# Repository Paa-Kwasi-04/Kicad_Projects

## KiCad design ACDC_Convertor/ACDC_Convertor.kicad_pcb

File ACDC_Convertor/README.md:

# ACDC Convertor

## Description
This is an AC-to-DC converter (rectifier) circuit board designed to convert alternating current (AC) to direct current (DC). The board includes rectification, filtering, and voltage regulation components to provide a stable DC output from an AC input source.

## Features
- AC to DC power conversion
- Filtering and voltage regulation
- Suitable for powering DC electronic devices from AC mains
- Compact PCB design

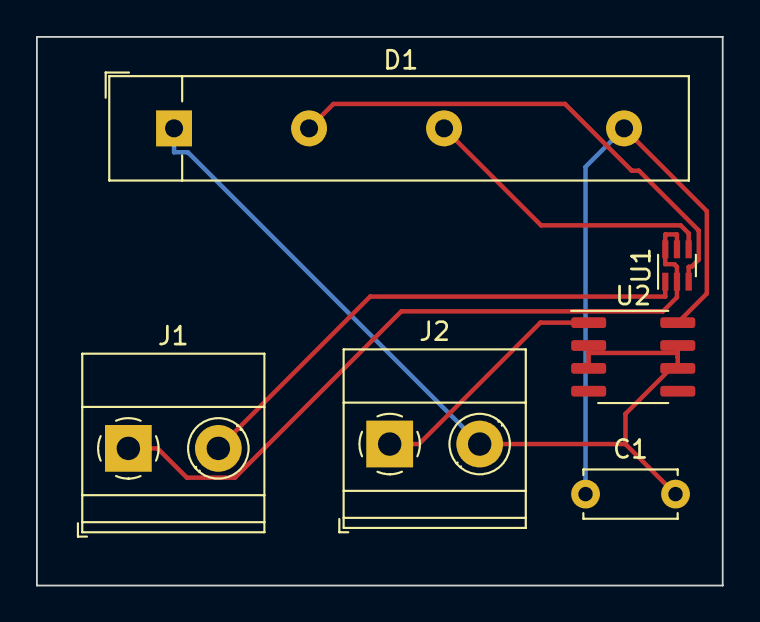
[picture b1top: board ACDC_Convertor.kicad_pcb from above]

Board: 2 copper layers, 38.1 x 30.5 mm, 6 parts (0 on the bottom side), 7 nets.

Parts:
C1: 100n; C_Disc_D5.0mm_W2.5mm_P5.00mm
D1: B40C5000-3x00A; Diode_Bridge_32.0x5.6x17.0mm_P10.0mm_P7.5mm
J1, J2: Screw_Terminal_01x02; TerminalBlock_Phoenix_MKDS-1,5-2_1x02_P5.00mm_Horizontal
U1: 0433BM15A0001; Balun_Johanson_0896BM15A0001
U2: L78L12_SO8; SOIC-8_3.9x4.9mm_P1.27mm

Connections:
unnamed: C1.1, D1.4 (+), U2.8 (IN)
unnamed: C1.2, D1.1 (-), J2.2, U2.2 (GND), U2.3 (GND), U2.6 (GND), U2.7 (GND)
unnamed: D1.2, U1.3
unnamed: D1.3, U1.4
unnamed: J1.1, U1.2 (GND), U1.5 (GND), U1.6 (GND)
unnamed: J1.2, U1.1
unnamed: J2.1, U2.1 (OUT)

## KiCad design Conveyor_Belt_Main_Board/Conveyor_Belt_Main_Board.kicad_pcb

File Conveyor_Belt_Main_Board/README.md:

# Conveyor Belt Main Board

## Description
This is the main control board for an automated conveyor belt system. The board features an ATmega328P microcontroller, TB6600 stepper motor driver interface, I2C multiplexer (TCA9548A) for managing multiple sensors, and various connectors for IR sensors and control inputs. It provides complete control and monitoring for industrial or automated conveyor systems.

## Features
- ATmega328P microcontroller for main control
- TB6600 stepper motor driver integration
- TCA9548A I2C multiplexer for multiple sensor channels (8 channels)
- E3F1-3DN1 IR sensor support for object detection
- 5V/5A buck converter for power regulation
- ISP programming header
- Multiple sensor and control connectors
- Reset and start/stop button inputs

## Components
See the [List of Components](List%20Of%20Components.txt) for detailed component specifications.

## Block Diagram

## PCB Design

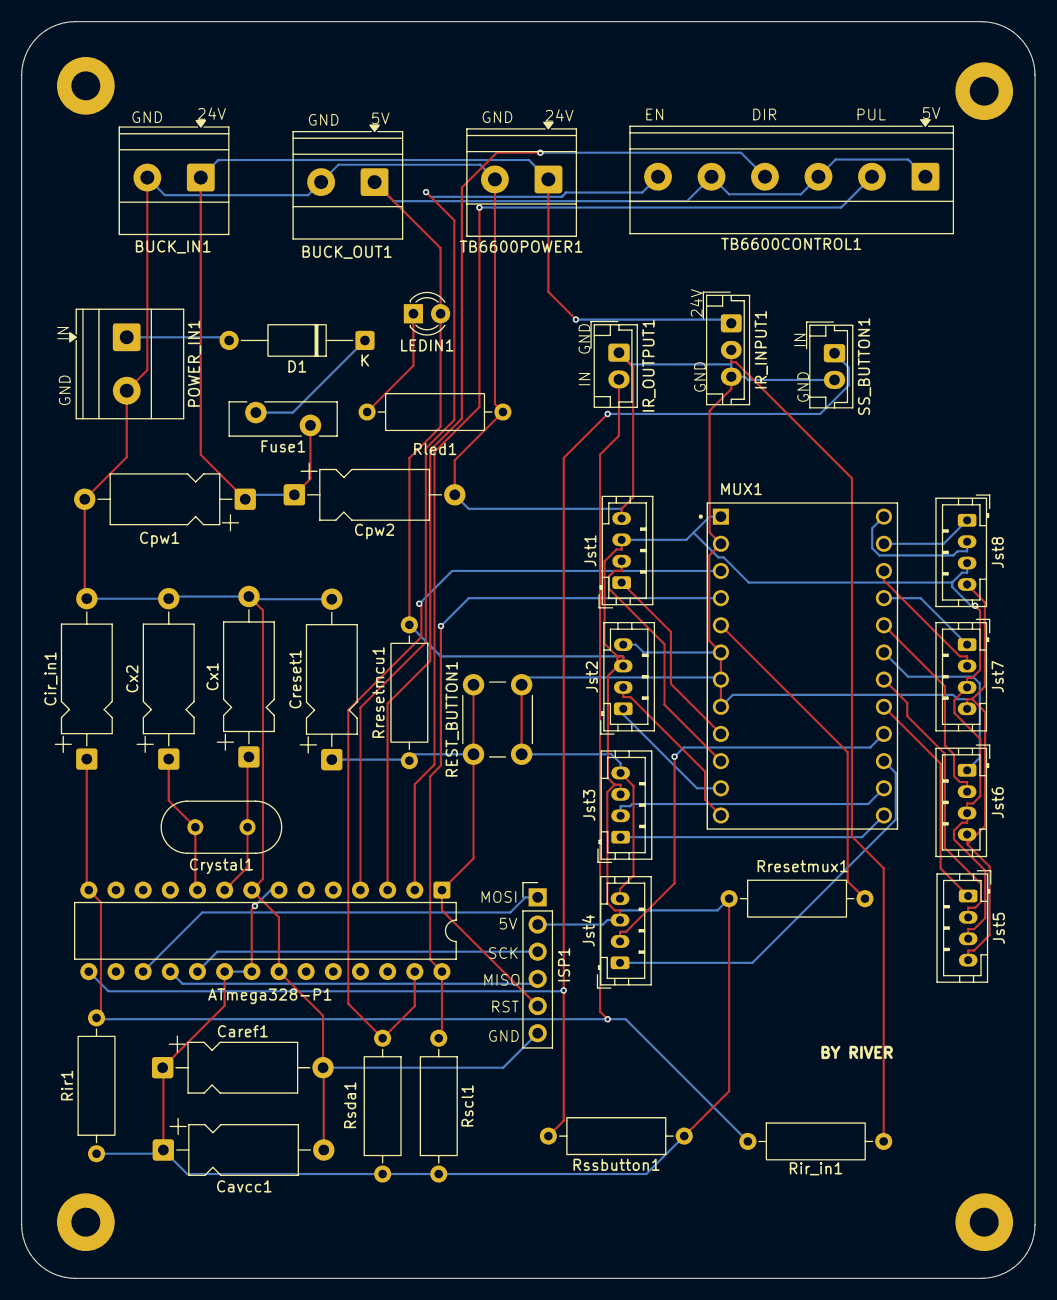
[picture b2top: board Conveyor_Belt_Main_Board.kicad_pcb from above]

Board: 2 copper layers, 94.8 x 117.5 mm, 44 parts (0 on the bottom side), 37 nets.

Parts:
ATmega328-P1: ATmega328-P; DIP-28_W7.62mm
BUCK_IN1: IN24V; TerminalBlock_Phoenix_MKDS-1,5-2_1x02_P5.00mm_Horizontal
BUCK_OUT1: OUT5V; TerminalBlock_Phoenix_MKDS-1,5-2_1x02_P5.00mm_Horizontal
Caref1: 10nF; CP_Axial_L10.0mm_D4.5mm_P15.00mm_Horizontal
Cavcc1: 0.1uF; CP_Axial_L10.0mm_D4.5mm_P15.00mm_Horizontal
Cir_in1: 10uF; CP_Axial_L10.0mm_D4.5mm_P15.00mm_Horizontal
Cpw1: 470uF; CP_Axial_L10.0mm_D4.5mm_P15.00mm_Horizontal
Cpw2: 0.1uF; CP_Axial_L10.0mm_D4.5mm_P15.00mm_Horizontal
Creset1: 0.1uF; CP_Axial_L10.0mm_D4.5mm_P15.00mm_Horizontal
Crystal1: 16MHz; Crystal_HC49-4H_Vertical
Cx1, Cx2: 22pF; CP_Axial_L10.0mm_D4.5mm_P15.00mm_Horizontal
D1: D1sch; D_A-405_P12.70mm_Horizontal
Fuse1: PTCFuse; Fuse_Bourns_MF-RG400
H1, H2, H3, H4: MountingHole; MountingHole_2.7mm_Pad
IR_INPUT1: IR_IN; JST_EH_B3B-EH-A_1x03_P2.50mm_Vertical
IR_OUTPUT1: IR_OUT; JST_EH_B2B-EH-A_1x02_P2.50mm_Vertical
ISP1: ISP; PinHeader_1x06_P2.54mm_Vertical
Jst1: CH1; JST_PH_B4B-PH-K_1x04_P2.00mm_Vertical
Jst2: CH2; JST_PH_B4B-PH-K_1x04_P2.00mm_Vertical
Jst3: CH3; JST_PH_B4B-PH-K_1x04_P2.00mm_Vertical
Jst4: CH4; JST_PH_B4B-PH-K_1x04_P2.00mm_Vertical
Jst5: CH5; JST_PH_B4B-PH-K_1x04_P2.00mm_Vertical
Jst6: CH6; JST_PH_B4B-PH-K_1x04_P2.00mm_Vertical
Jst7: CH7; JST_PH_B4B-PH-K_1x04_P2.00mm_Vertical
Jst8: CH8; JST_PH_B4B-PH-K_1x04_P2.00mm_Vertical
LEDIN1: LED; LED_D3.0mm
MUX1: MUX; TCA954A_Multiplexer
POWER_IN1: IN24V; TerminalBlock_Phoenix_MKDS-1,5-2_1x02_P5.00mm_Horizontal
REST_BUTTON1: RST_BTN; SW_PUSH_6mm
Rir1: 10KΩ; R_Axial_DIN0309_L9.0mm_D3.2mm_P12.70mm_Horizontal
Rir_in1: 1KΩ; R_Axial_DIN0309_L9.0mm_D3.2mm_P12.70mm_Horizontal
Rled1: 330Ω; R_Axial_DIN0309_L9.0mm_D3.2mm_P12.70mm_Horizontal
Rresetmcu1: 10KΩ; R_Axial_DIN0309_L9.0mm_D3.2mm_P12.70mm_Horizontal
Rresetmux1: 10KΩ; R_Axial_DIN0309_L9.0mm_D3.2mm_P12.70mm_Horizontal
Rscl1: 4.7KΩ; R_Axial_DIN0309_L9.0mm_D3.2mm_P12.70mm_Horizontal
Rsda1: 4.7KΩ; R_Axial_DIN0309_L9.0mm_D3.2mm_P12.70mm_Horizontal
Rssbutton1: 10KΩ; R_Axial_DIN0309_L9.0mm_D3.2mm_P12.70mm_Horizontal
SS_BUTTON1: SS_B; JST_EH_B2B-EH-A_1x02_P2.50mm_Vertical
TB6600CONTROL1: CONTROL; TerminalBlock_Phoenix_MKDS-1,5-6_1x06_P5.00mm_Horizontal
TB6600POWER1: POWER24V; TerminalBlock_Phoenix_MKDS-1,5-2_1x02_P5.00mm_Horizontal

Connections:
/5V: ATmega328-P1.7 (VCC), ATmega328-P1.20 (AVCC), ATmega328-P1.21 (AREF), BUCK_OUT1.1, Caref1.1, Cavcc1.1, ISP1.2 (VCC), Jst1.3, Jst2.3, Jst3.3, Jst4.3, Jst5.3, Jst6.3, Jst7.3, Jst8.3, LEDIN1.2 (A), MUX1.1 (VIN), Rir1.1, Rresetmcu1.1, Rresetmux1.1, Rscl1.2, Rsda1.2, Rssbutton1.1, TB6600CONTROL1.1, TB6600CONTROL1.3, TB6600CONTROL1.5
/24V: BUCK_IN1.1, Cpw1.1, Cpw2.1, Fuse1.2, IR_INPUT1.1, TB6600POWER1.1
/DIR: ATmega328-P1.3 (PD1), TB6600CONTROL1.4
/EN: ATmega328-P1.4 (PD2), TB6600CONTROL1.6
/IR_IN: ATmega328-P1.14 (PB0), Cir_in1.1, IR_OUTPUT1.2, Rir1.2, Rir_in1.1
/MISO: ATmega328-P1.18 (PB4), ISP1.4 (MOSI)
/MOSI: ATmega328-P1.17 (PB3), ISP1.1 (MISO)
/PUL: ATmega328-P1.2 (PD0), TB6600CONTROL1.2
/RST: ATmega328-P1.1 (~RESET/PC6), Creset1.1, ISP1.5 (~RST), REST_BUTTON1.1, Rresetmcu1.2
/SC0: Jst1.2, MUX1.10 (SCL0)
/SC1: Jst2.2, MUX1.12 (SCL1)
/SC2: Jst3.2, MUX1.14 (SCL2)
/SC3: Jst4.2, MUX1.16 (SCL3)
/SC4: Jst5.2, MUX1.18 (SCL4)
/SC5: Jst6.2, MUX1.20 (SCL5)
/SC6: Jst7.2, MUX1.22 (SCL6)
/SC7: Jst8.2, MUX1.24 (SCL7)
/SCK: ATmega328-P1.19 (PB5), ISP1.3 (SCK)
/SCL: ATmega328-P1.28 (PC5), MUX1.4 (SCL), Rscl1.1
/SD0: Jst1.1, MUX1.9 (SDA0)
/SD1: Jst2.1, MUX1.11 (SDA1)
/SD2: Jst3.1, MUX1.13 (SDA2)
/SD3: Jst4.1, MUX1.15 (SDA3)
/SD4: Jst5.1, MUX1.17 (SDA4)
/SD5: Jst6.1, MUX1.19 (SDA5)
/SD6: Jst7.1, MUX1.21 (SDA6)
/SD7: Jst8.1, MUX1.23 (SDA7)
/SDA: ATmega328-P1.27 (PC4), MUX1.3 (SDA), Rsda1.1
/S/S button: ATmega328-P1.15 (PB1), Rssbutton1.2, SS_BUTTON1.1
GND: ATmega328-P1.8 (GND), ATmega328-P1.22 (GND), BUCK_IN1.2, BUCK_OUT1.2, Caref1.2, Cavcc1.2, Cir_in1.2, Cpw1.2, Cpw2.2, Creset1.2, Cx1.2, Cx2.2, IR_INPUT1.3, IR_OUTPUT1.1, ISP1.6 (GND), Jst1.4, Jst2.4, Jst3.4, Jst4.4, Jst5.4, Jst6.4, Jst7.4, Jst8.4, MUX1.2 (GND), MUX1.6 (A0), MUX1.7 (A1), MUX1.8 (A2), POWER_IN1.2, REST_BUTTON1.2, Rled1.2, SS_BUTTON1.2, TB6600POWER1.2
unnamed: ATmega328-P1.9 (XTAL1/PB6), Crystal1.1, Cx1.1
unnamed: ATmega328-P1.10 (XTAL2/PB7), Crystal1.2, Cx2.1
unnamed: D1.2 (A), POWER_IN1.1
unnamed: D1.1 (K), Fuse1.1
unnamed: IR_INPUT1.2, Rir_in1.2
unnamed: LEDIN1.1 (K), Rled1.1
unnamed: MUX1.5 (RST), Rresetmux1.2

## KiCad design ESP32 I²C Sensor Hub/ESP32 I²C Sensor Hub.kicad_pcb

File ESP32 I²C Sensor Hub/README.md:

# ESP32 I²C Sensor Hub

## Description
This project is a specialized ESP32-based board designed to serve as a central hub for multiple I²C sensors. The board leverages the ESP32's wireless connectivity to collect data from various I²C sensors and transmit it wirelessly or process it locally. Ideal for distributed sensor networks and IoT monitoring applications.

## Features
- ESP32 microcontroller with Wi-Fi and Bluetooth
- Multiple I²C sensor connections
- Acts as a sensor data aggregation hub
- Wireless data transmission capability
- Suitable for environmental monitoring and IoT projects

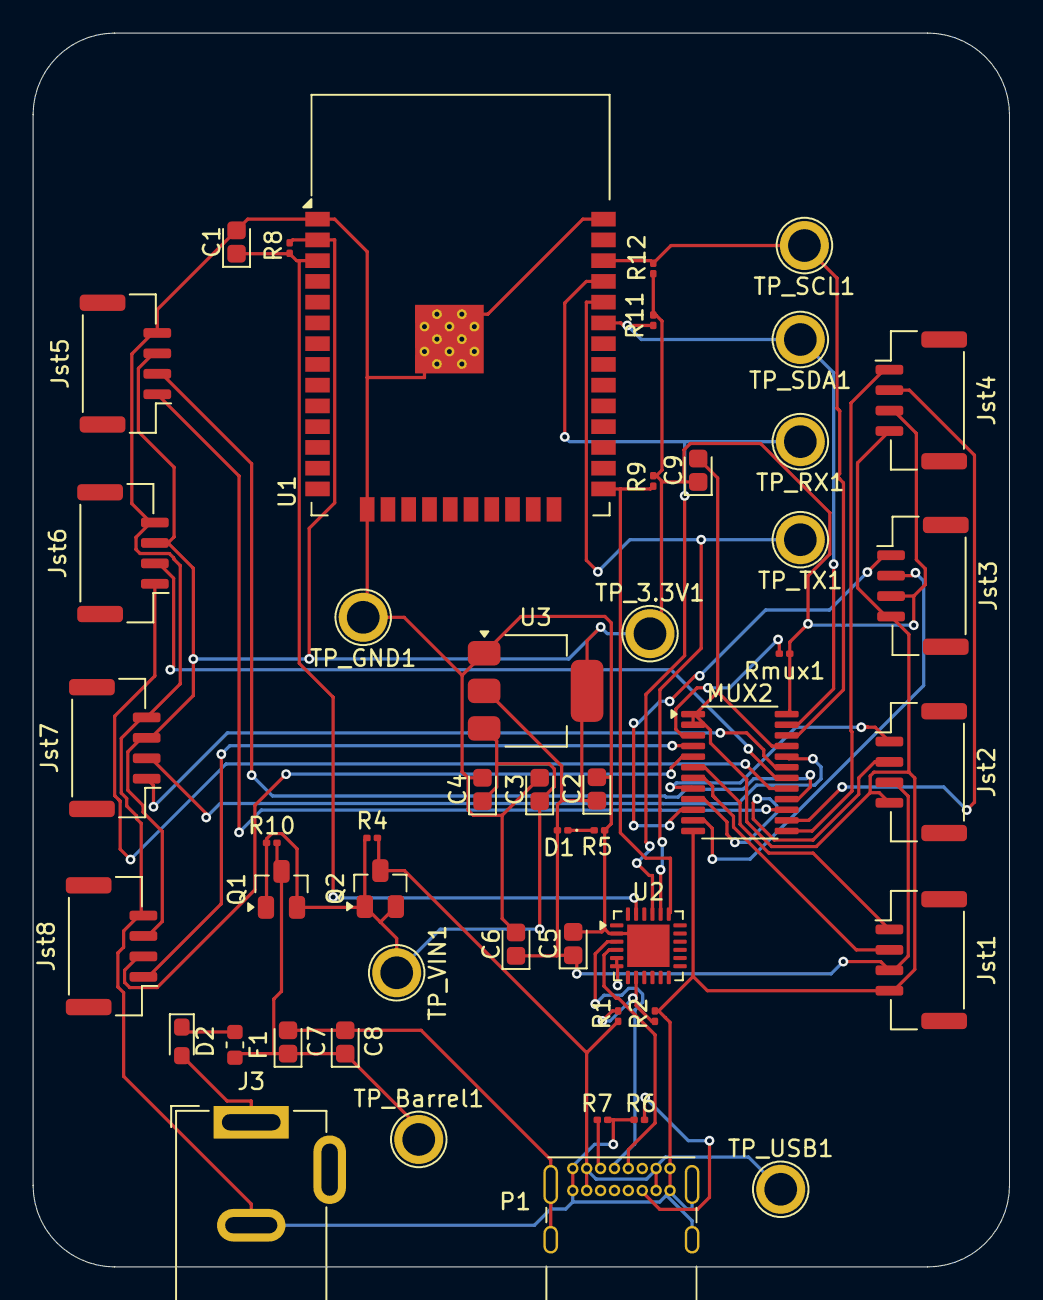
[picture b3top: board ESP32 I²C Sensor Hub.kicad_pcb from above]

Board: 2 copper layers, 59.8 x 75.5 mm, 49 parts (0 on the bottom side), 36 nets.

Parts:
C1: 100nF; CP_EIA-1608-10_AVX-L
C2, C3, C5, C6, C9: 0.1µF; CP_EIA-1608-10_AVX-L
C4: 10µF; CP_EIA-1608-10_AVX-L
C7: 470uF; CP_EIA-1608-10_AVX-L
C8: 0.1uF; CP_EIA-1608-10_AVX-L
D1: LED; LED_0201_0603Metric
D2: SS14; D_0603_1608Metric_Pad1.05x0.95mm_HandSolder
F1: Fuse; Fuse_0603_1608Metric
J3: Barrel_Jack; BarrelJack_GCT_DCJ200-10-A_Horizontal
Jst1, Jst2, Jst3, Jst4, Jst5, Jst6, Jst7, Jst8: SM04B-SRSS-TB; JST_GH_BM04B-GHS-TBT_1x04-1MP_P1.25mm_Vertical
MUX2: TCA9548APWR; TSSOP-24_4.4x7.8mm_P0.65mm
P1: USB_C_Plug_USB2.0; USB_C_Receptacle_GCT_USB4085
Q1, Q2: PMOS; SuperSOT-3
R1, R6, R7: 5.1KΩ; R_0201_0603Metric
R2, R8, R9, R11, R12: 10KΩ; R_0201_0603Metric
R4, R10: 100KΩ; R_0201_0603Metric
R5: 330Ω; R_0201_0603Metric
Rmux1: 10k; R_0201_0603Metric
TP_3.3V1: TestPoint_3.3V; TestPoint_Plated_Hole_D2.0mm
TP_Barrel1: TestPoint_Barrel; TestPoint_Plated_Hole_D2.0mm
TP_GND1: TestPoint_GND; TestPoint_Plated_Hole_D2.0mm
TP_RX1: TestPoint_RX; TestPoint_Plated_Hole_D2.0mm
TP_SCL1: TestPoint_SCL; TestPoint_Plated_Hole_D2.0mm
TP_SDA1: TestPoint_SDA; TestPoint_Plated_Hole_D2.0mm
TP_TX1: TestPoint_TX; TestPoint_Plated_Hole_D2.0mm
TP_USB1: TestPoint_USB; TestPoint_Plated_Hole_D2.0mm
TP_VIN1: TestPoint_VIN; TestPoint_Plated_Hole_D2.0mm
U1: ESP32-WROOM-32
U2: CP2102N-Axx-xQFN24; QFN-24-1EP_4x4mm_P0.5mm_EP2.6x2.6mm
U3: AMS1117-3.3; SOT-223-3_TabPin2

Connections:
/Barrel_POWER: C7.1, C8.1, F1.2, Q1.3 (S), R10.2, TP_Barrel1.1
/D+: P1.A6 (D+), U2.3 (D+)
/D-: P1.A7 (D-), U2.4 (D-)
/DTR_EN: C1.1, R8.2, U1.3 (EN), U2.23 (~DTR)
/RTS_IO0: R9.2, U1.25 (IO0), U2.19 (~RTS)
/RX: TP_RX1.1, U1.35 (TXD0/IO1), U2.21 (TXD)
/SC0: Jst8.2, MUX2.5 (SC0)
/SC1: Jst1.2, MUX2.7 (SC1)
/SC2: Jst2.2, MUX2.9 (SC2)
/SC3: Jst3.2, MUX2.11 (SC3)
/SC4: Jst4.2, MUX2.14 (SC4)
/SC5: Jst5.2, MUX2.16 (SC5)
/SC6: Jst6.2, MUX2.18 (SC6)
/SC7: Jst7.2, MUX2.20 (SC7)
/SCL: MUX2.22 (SCL), R12.2, TP_SCL1.1, U1.36 (IO22)
/SD0: Jst8.1, MUX2.4 (SD0)
/SD1: Jst1.1, MUX2.6 (SD1)
/SD2: Jst2.1, MUX2.8 (SD2)
/SD3: Jst3.1, MUX2.10 (SD3)
/SD4: Jst4.1, MUX2.13 (SD4)
/SD5: Jst5.1, MUX2.15 (SD5)
/SD6: Jst6.1, MUX2.17 (SD6)
/SD7: Jst7.1, MUX2.19 (SD7)
/SDA: MUX2.23 (SDA), R11.2, TP_SDA1.1, U1.33 (IO21)
/TX: TP_TX1.1, U1.34 (RXD0/IO3), U2.20 (RXD)
/USB_POWER: P1.A4 (VBUS), P1.A9 (VBUS), P1.B4 (VBUS), P1.B9 (VBUS), Q2.3 (S), R1.2, R4.2, TP_USB1.1
/VREG_IN_POWER: C3.1, C4.1, Q1.1 (D), Q1.2 (G), Q2.1 (D), Q2.2 (G), R4.1, R10.1, TP_VIN1.1, U3.3 (VI)
/Vcc3.3V_POWER: C2.1, C5.1, C6.1, C9.1, D1.2 (A), Jst1.3, Jst2.3, Jst3.3, Jst4.3, Jst5.3, Jst6.3, Jst7.3, Jst8.3, MUX2.24 (VCC), R8.1, R9.1, R11.1, R12.1, Rmux1.1, TP_3.3V1.1, U1.2 (VDD), U2.5 (VIO), U2.6 (VDD), U3.2 (VO)
GND: C1.2, C2.2, C3.2, C4.2, C5.2, C6.2, C7.2, C8.2, C9.2, J3.2, Jst1.4, Jst2.4, Jst3.4, Jst4.4, Jst5.4, Jst6.4, Jst7.4, Jst8.4, MUX2.1 (A0), MUX2.2 (A1), MUX2.12 (GND), MUX2.21 (A2), P1.A1 (GND), P1.A12 (GND), P1.B1 (GND), P1.B12 (GND), P1.S1 (SHIELD), R2.1, R5.2, R6.2, R7.2, TP_GND1.1, U1.1 (GND), U1.15 (GND), U1.38 (GND), U1.39 (GND), U2.2 (GND), U2.25 (GND), U3.1 (GND)
unnamed: D1.1 (K), R5.1
unnamed: D2.2 (A), J3.1
unnamed: D2.1 (K), F1.1
unnamed: MUX2.3 (~RESET), Rmux1.2
unnamed: P1.A5 (CC), R7.1
unnamed: P1.B5 (VCONN), R6.1
unnamed: R1.1, R2.2, U2.8 (VBUS)

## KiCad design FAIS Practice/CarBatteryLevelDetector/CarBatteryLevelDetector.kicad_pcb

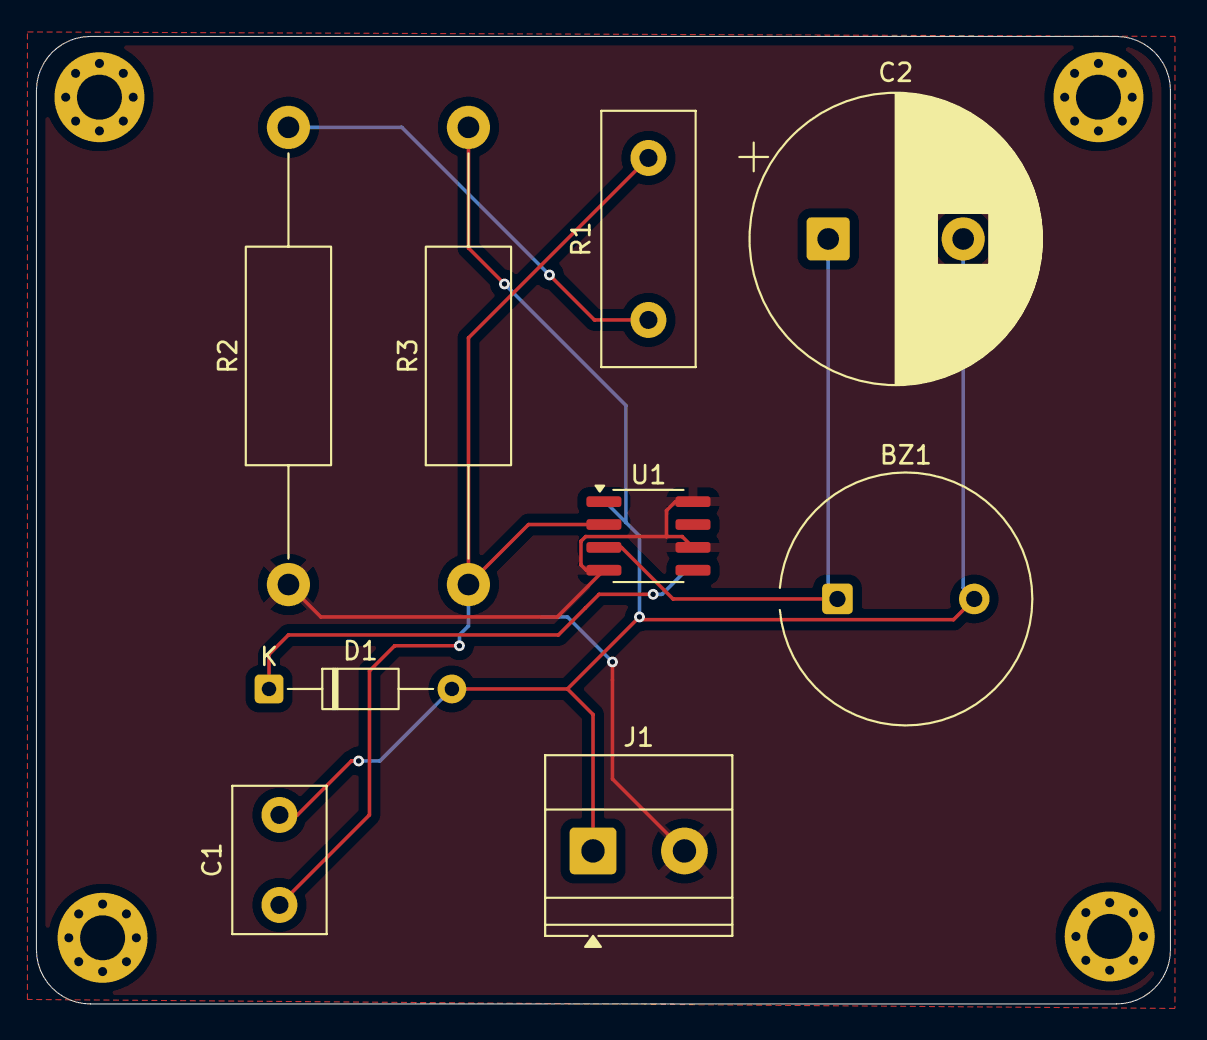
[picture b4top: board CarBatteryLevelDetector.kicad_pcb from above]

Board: 2 copper layers, 63.0 x 53.8 mm, 13 parts (0 on the bottom side), 6 nets.

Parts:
BZ1: Buzzer; Indicator_PUI_AI-1440-TWT-24V-2-R
C1: 10n; C_Disc_D8.0mm_W5.0mm_P5.00mm
C2: 470UF; CP_Radial_D16.0mm_P7.50mm
D1: 3.3v; D_DO-35_SOD27_P10.16mm_Horizontal
H1, H2, H3, H4: MountingHole_Pad; MountingHole_2.5mm_Pad_Via
J1: Screw_Terminal_01x02; TerminalBlock_Phoenix_MKDS-1,5-2-5.08_1x02_P5.08mm_Horizont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
R1: 10k; R_Box_L14.0mm_W5.0mm_P9.00mm
R2: 27k; R_Axial_DIN0414_L11.9mm_D4.5mm_P25.40mm_Horizontal
R3: 8.2k; R_Axial_DIN0414_L11.9mm_D4.5mm_P25.40mm_Horizontal
U1: NE555D; SOIC-8_3.9x4.9mm_P1.27mm

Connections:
+5V: J1.2, R2.1, U1.4 (R), U1.6 (THR), U1.8 (VCC)
GND: BZ1.2 (-), C1.2, C2.2, D1.2 (A), J1.1, R3.2, U1.1 (GND)
unnamed: BZ1.1 (+), C2.1, U1.3 (Q)
unnamed: D1.1 (K), U1.5 (CV)
unnamed: R1.1, R2.2
unnamed: C1.1, R1.2, R3.1, U1.2 (TR)

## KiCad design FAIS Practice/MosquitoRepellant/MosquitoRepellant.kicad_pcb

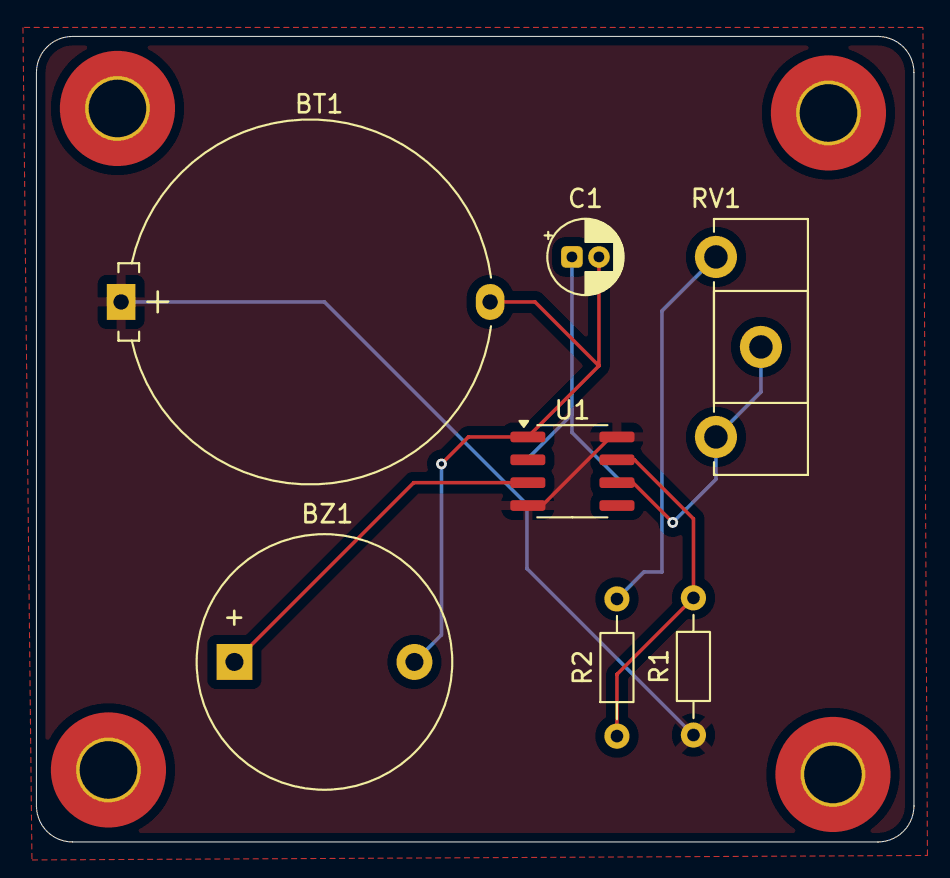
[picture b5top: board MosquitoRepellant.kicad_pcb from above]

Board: 2 copper layers, 48.8 x 44.8 mm, 11 parts (0 on the bottom side), 6 nets.

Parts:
BT1: 9; Battery_Panasonic_CR2032-HFN_Horizontal_CircularHoles
BZ1: Buzzer; Buzzer_D14mm_H7mm_P10mm
C1: 0.1u; CP_Radial_D4.0mm_P1.50mm
H1, H2, H3, H4: MountingHole; MountingHole_3.2mm_M3_Pad_TopOnly
R1: 3.3k; R_Axial_DIN0204_L3.6mm_D1.6mm_P7.62mm_Horizontal
R2: 2.2k; R_Axial_DIN0204_L3.6mm_D1.6mm_P7.62mm_Horizontal
RV1: R_Potentiometer_Trim; Potentiometer_ACP_CA14-H2,5_Horizontal
U1: NE555D; SOIC-8_3.9x4.9mm_P1.27mm

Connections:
+5V: BT1.1 (+), R1.1, U1.4 (R), U1.8 (VCC)
GND: BT1.2 (-), BZ1.2 (-), C1.2, U1.1 (GND)
unnamed: BZ1.1 (+), U1.3 (Q)
unnamed: R2.2, RV1.1
unnamed: R1.2, R2.1, U1.7 (DIS)
unnamed: C1.1, RV1.2, RV1.3, U1.2 (TR), U1.6 (THR)

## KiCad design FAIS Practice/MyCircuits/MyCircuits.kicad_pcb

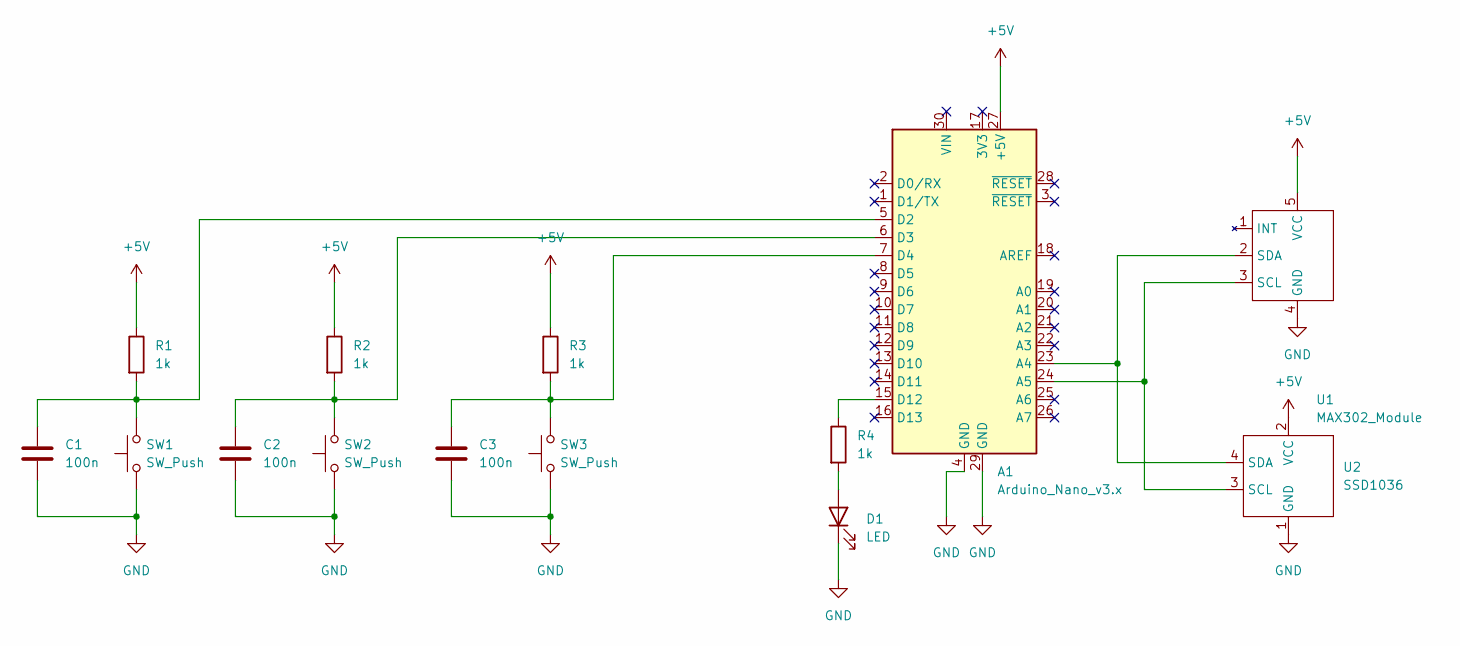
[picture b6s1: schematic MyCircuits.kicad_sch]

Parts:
A1: Arduino_Nano_v3.x; Arduino_Nano
C1, C2, C3: 100n; C_Disc_D4.3mm_W1.9mm_P5.00mm
D1: LED; LED_D5.0mm
R1, R2, R3, R4: 1k; R_Axial_DIN0207_L6.3mm_D2.5mm_P7.62mm_Horizontal
SW1, SW2, SW3: SW_Push; SW_PUSH_6mm
U1: MAX302_Module; MAX3103_Module
U2: SSD1036

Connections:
+5V: A1.27 (+5V), R1.1, R2.1, R3.1, U1.5 (VCC), U2.2 (VCC)
GND: A1.4 (GND), A1.29 (GND), C1.2, C2.2, C3.2, D1.1 (K), SW1.1, SW2.1, SW3.1, U1.4 (GND), U2.1 (GND)
unnamed: A1.5 (D2), C1.1, R1.2, SW1.2
unnamed: A1.6 (D3), C2.1, R2.2, SW2.2
unnamed: A1.7 (D4), C3.1, R3.2, SW3.2
unnamed: A1.15 (D12), R4.1
unnamed: A1.23 (A4), U1.2 (SDA), U2.4 (SDA)
unnamed: A1.24 (A5), U1.3 (SCL), U2.3 (SCL)
unnamed: D1.2 (A), R4.2

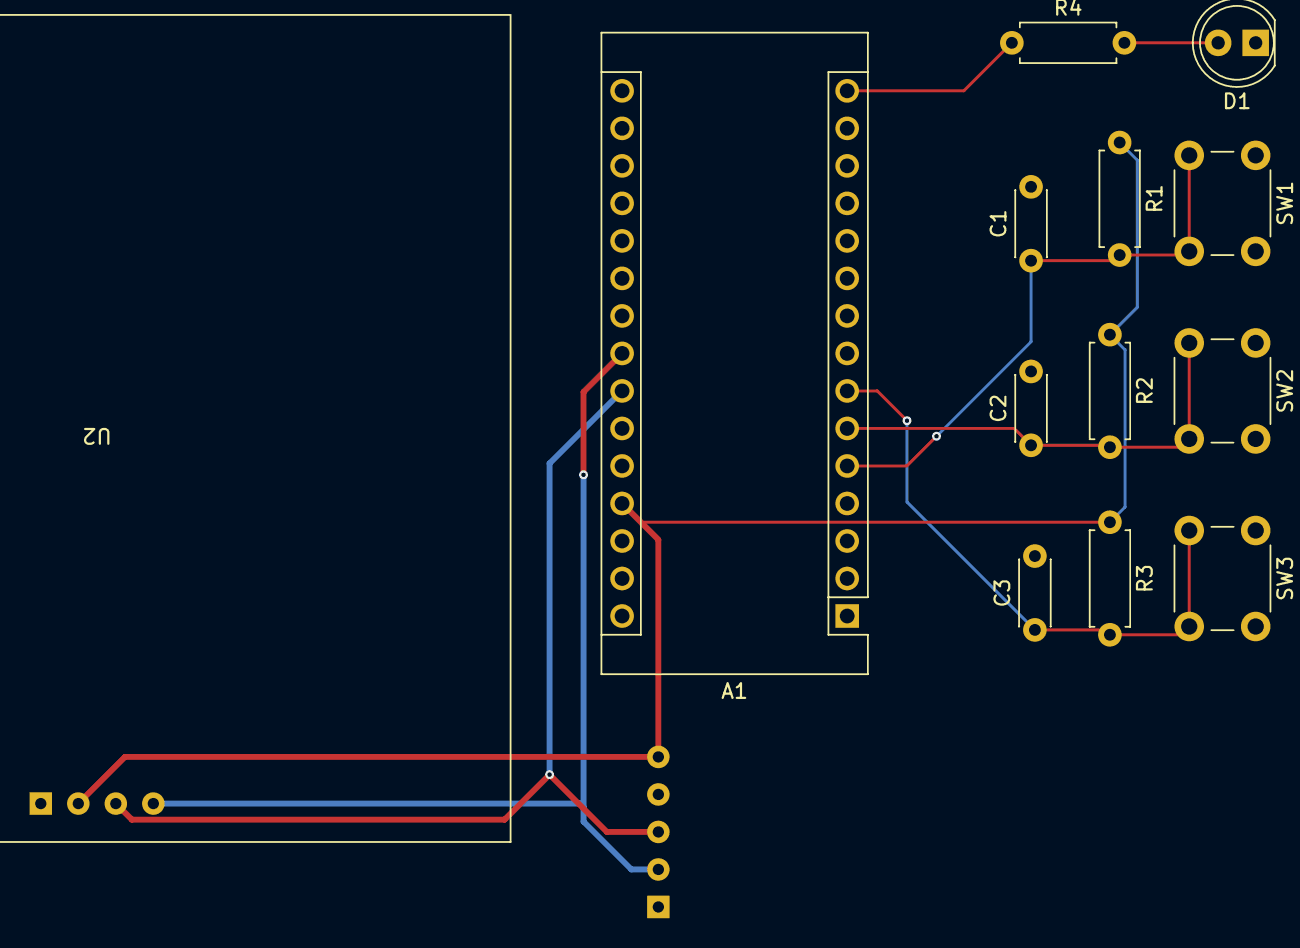
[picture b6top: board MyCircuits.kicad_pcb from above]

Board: 2 copper layers, 14 parts (1 on the bottom side), 9 nets.

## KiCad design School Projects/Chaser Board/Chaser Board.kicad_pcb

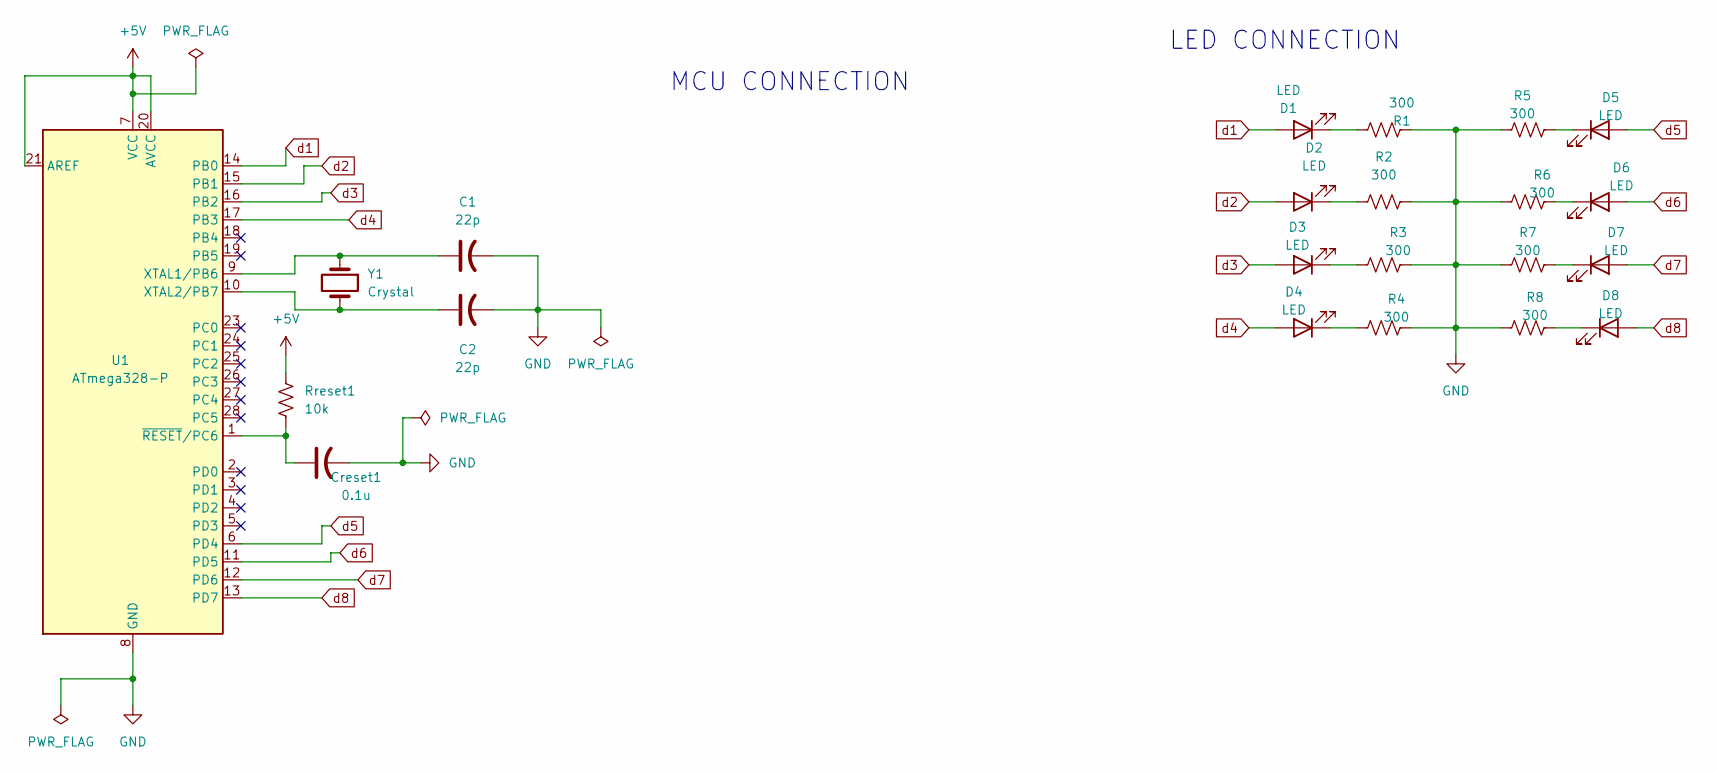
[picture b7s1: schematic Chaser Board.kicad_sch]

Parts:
C1, C2: 22p
Creset1: 0.1u
D1, D2, D3, D4, D5, D6, D7, D8: LED
R1, R2, R3, R4, R5, R6, R7, R8: 300
Rreset1: 10k
U1: ATmega328-P; DIP-28_W7.62mm
Y1: Crystal

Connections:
+5V: Rreset1.1, U1.7 (VCC), U1.20 (AVCC), U1.21 (AREF)
GND: C1.2, C2.2, Creset1.2, R1.1, R2.2, R3.2, R4.2, R5.1, R6.1, R7.1, R8.1, U1.8 (GND), U1.22 (GND)
unnamed: D1.1 (K), R1.2
unnamed: D2.1 (K), R2.1
unnamed: D3.1 (K), R3.1
unnamed: D4.1 (K), R4.1
unnamed: D5.1 (K), R5.2
unnamed: D6.1 (K), R6.2
unnamed: D7.1 (K), R7.2
unnamed: D8.1 (K), R8.2
unnamed: C1.1, U1.9 (XTAL1/PB6), Y1.1
unnamed: C2.1, U1.10 (XTAL2/PB7), Y1.2
unnamed: Creset1.1, Rreset1.2, U1.1 (~RESET/PC6)
d1: D1.2 (A), U1.14 (PB0)
d2: D2.2 (A), U1.15 (PB1)
d3: D3.2 (A), U1.16 (PB2)
d4: D4.2 (A), U1.17 (PB3)
d5: D5.2 (A), U1.6 (PD4)
d6: D6.2 (A), U1.11 (PD5)
d7: D7.2 (A), U1.12 (PD6)
d8: D8.2 (A), U1.13 (PD7)

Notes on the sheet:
LED CONNECTION
MCU CONNECTION

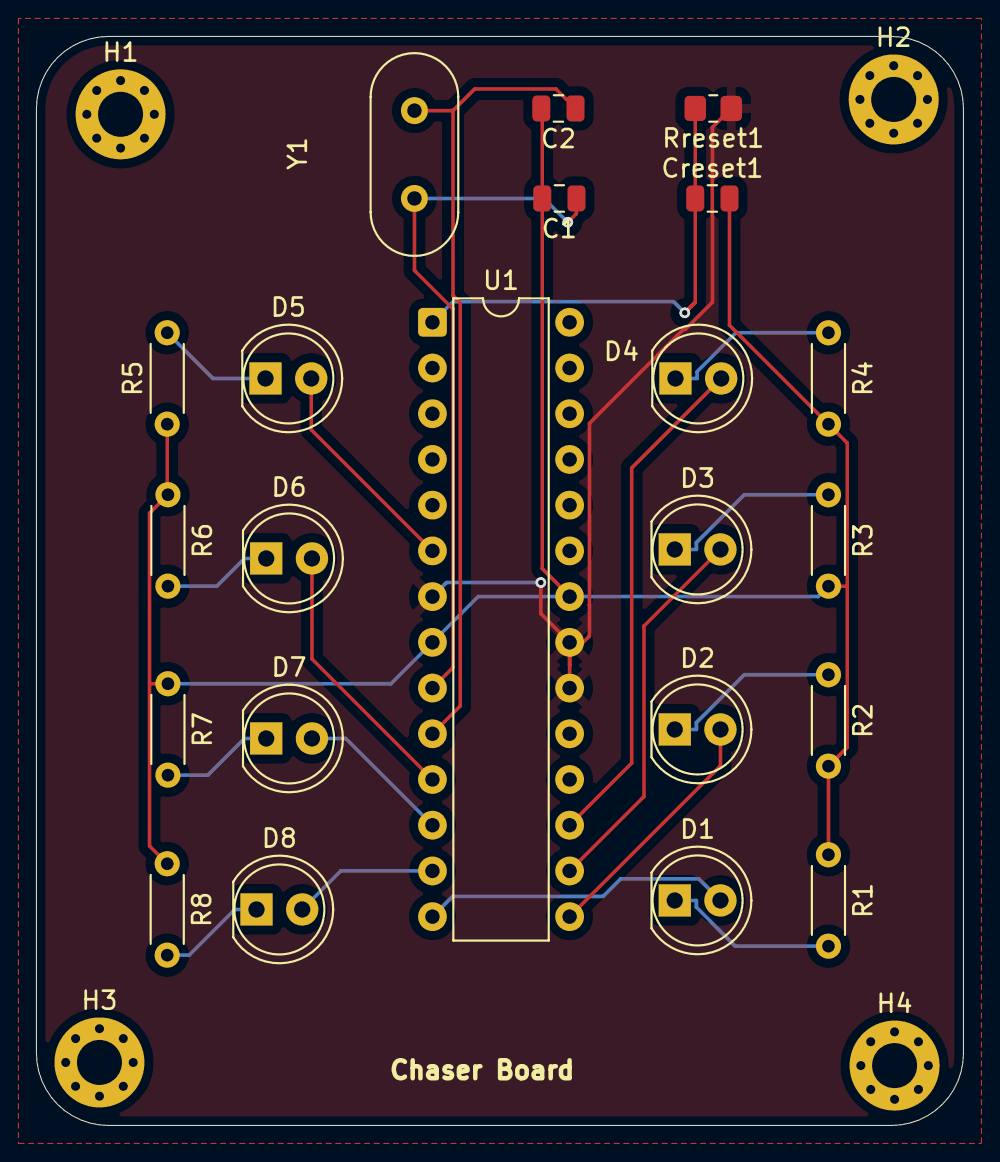
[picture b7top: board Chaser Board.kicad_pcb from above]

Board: 2 copper layers, 51.5 x 60.5 mm, 26 parts (0 on the bottom side), 21 nets.

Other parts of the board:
H1, H2, H3, H4: MountingHole; MountingHole_2.5mm_Pad_Via

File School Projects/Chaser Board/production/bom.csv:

Designator,Footprint,Quantity,Value,LCSC Part #
"C1, C2",805,2,22p,
CRESET1,805,1,0.1u,
"D1, D2, D3, D4, D5, D6, D7, D8",LED_D5.0mm,8,LED,
"R1, R2, R3, R4, R5, R6, R7, R8",R_Axial_DIN0204_L3.6mm_D1.6mm_P5.08mm_Horizontal,8,300,
RRESET1,805,1,10k,
U1,DIP-28_W7.62mm,1,ATmega328-P,
Y1,Crystal_HC49-4H_Vertical,1,Crystal,

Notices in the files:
parts and their libraries:
COPYRIGHT: Copyright (C) 2024 Ultra Librarian. All rights reserved.
